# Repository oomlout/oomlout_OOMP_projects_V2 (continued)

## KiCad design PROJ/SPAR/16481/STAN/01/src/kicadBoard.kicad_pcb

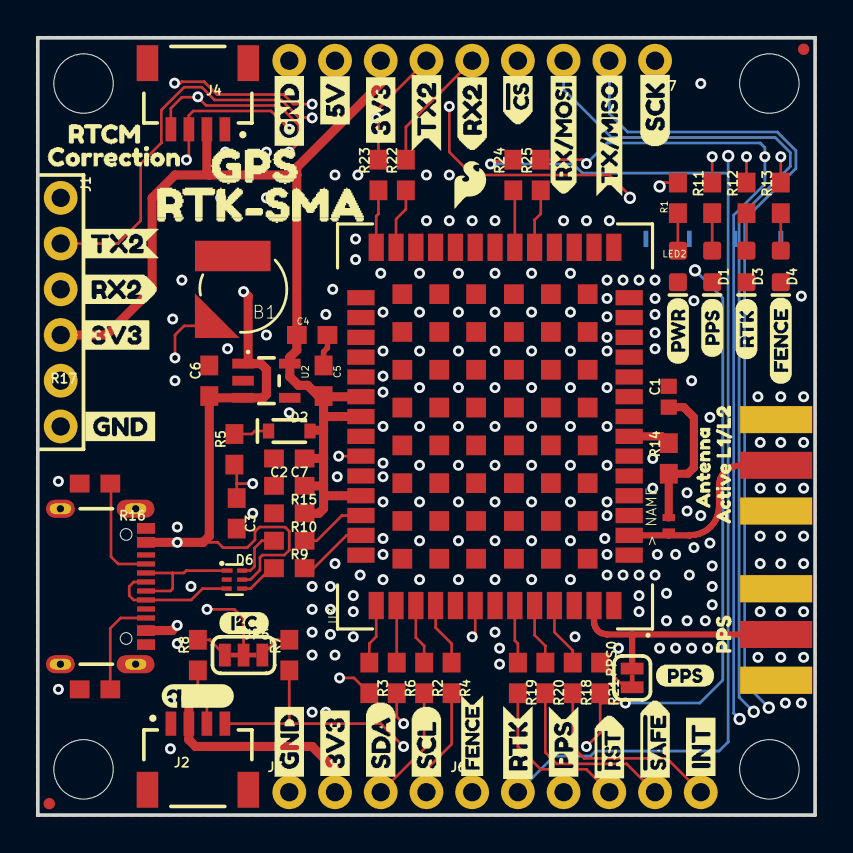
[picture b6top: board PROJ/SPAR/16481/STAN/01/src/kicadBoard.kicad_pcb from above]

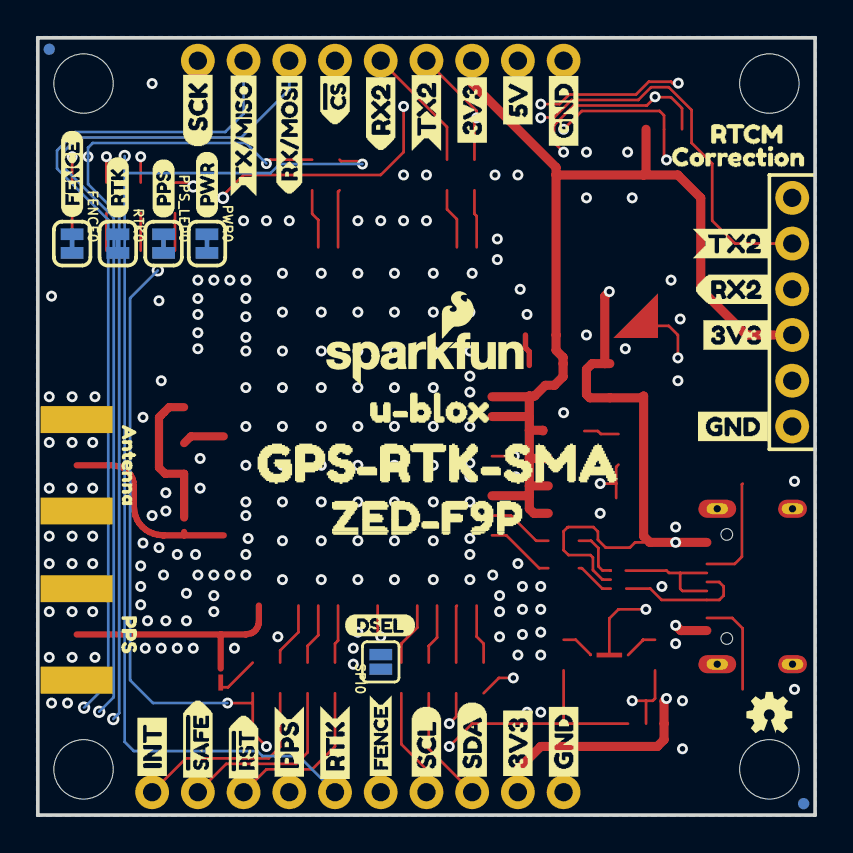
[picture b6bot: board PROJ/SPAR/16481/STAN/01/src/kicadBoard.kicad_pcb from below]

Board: 4 copper layers, 43.2 x 43.2 mm, 143 parts (44 on the bottom side), 52 nets.

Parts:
B1: 6.8MM_COIN_CELL; ML414H_IV01E
C1: 47pF; 0402
C2, C3, C4, C6: 1.0uF; 0603
C5, C7: 0.1uF; 0603
D1: Yellow; LED-0603
D2: 0.5A/40V/420mV; SOD-323
D3: GREEN; LED-0603
D4: BLUE; LED-0603
D6: PRTR5V0U2F; SOT886
E1, E2: SMA; SMA-EDGE
FB1: 120NH; 0402_MURATA
FENCE0: SMT-JUMPER_2_NC_TRACE_SILK
FRAME2: FRAME-LEDGER; CREATIVE_COMMONS
J1: Radio; 1X06_NO_SILK
J2, J4: Qwiic Right Angle; JST04_1MM_RA
J3: PTH; 1X04_NO_SILK
J5: USB-C-16P-2LAYER-PADS
J6: 1X06_NO_SILK
J7: 1X09_NO_SILK
JP5: SMT-JUMPER_3_2-NC_TRACE_SILK
JP21, JP61, JP71, JP81: FIDUCIALUFIDUCIAL; MICRO-FIDUCIAL
JP31, JP41, JP91, JP101: STAND-OFF
LED2: RED; LED-0603
LOGO1: OSHW-LOGOMINI; OSHW-LOGO-MINI
LOGO2: SFE_LOGO_NAME_FLAME.1_INCH; SFE_LOGO_NAME_FLAME_.1
PPS0: SMT-JUMPER_2_NC_TRACE_SILK
PPS_LED0: SMT-JUMPER_2_NC_TRACE_SILK
PWR0: SMT-JUMPER_2_NC_TRACE_SILK
R1, R5, R11, R12, R13: 1k; 0603
R2, R3, R4, R6, R14, R18, R19, R20, R21, R22, R23, R24, R25: 33; 0603
R7, R8: 2.2k; 0603
R9, R10: 27; 0603
R15: 100k; 0603
R16, R17: 5.1k; 0603
RTK0: SMT-JUMPER_2_NC_TRACE_SILK
SPI0: SMT-JUMPER_2_NO_SILK
U2: 3.3V; SOT23-5
U3: ZED-F9P
U$1, U$4: SDA-[)
U$2: SPECIAL_INSTRUCTIONS-ORDERING; ORDERING_INSTRUCTIONS
U$3, U$5: SCL-[)
U$6, U$7, U$60, U$61, U$66, U$67: 3V3-04
U$8, U$9, U$62, U$63: GND-04
U$10: I_SUPER2_C-()-03
U$11, U$54: FENCE2
U$12, U$18: PWR-()-03
U$13, U$28, U$29, U$32: RTK1
U$14, U$17: FENCE0
U$15, U$16: INT8
U$19, U$20: 5V
U$21, U$56, U$58: RX20
U$22: U#BLOX3
U$23, U$24: CS#-_]
U$25, U$52, U$72: PPS0
U$26, U$31: RX#MOSI3
U$27: DSEL0
U$30: QWIIC_4MM
U$33: SFE_LOGO_FLAME_.1
U$34, U$37: TX#MISO1
U$35, U$36: #RST3
U$38, U$41: SCK-(]-04
U$39, U$40: #SAFE1
U$42: RX22
U$43, U$44: PPS5
U$45, U$68: GND3
U$47, U$74: PPS1
U$48, U$70: RTCM5
U$49: ZED#F9P6
U$50, U$55, U$57: TX21
U$51: TX23
U$53, U$69: CORRECTION0
U$59: GPS0
U$65: ACTIVE_L1#L21
U$71, U$75: ANTENNA2
U$73: RTK#SMA4
U$76: GPS#RTK#SMA5

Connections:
3.3V: C2.1, C4.1, C5.2, C7.2, D2.A, J1.4, J2.2, J3.2, J4.2, J7.7, JP5.2, PWR0.2, R15.2, U2.5, U3.33, U3.34, U3.38
5V: C6.1, D6.5, J5.VBUS1, J5.VBUS2, J7.8, U2.1, U2.3
ANT_VCC: C1.1, FB1.P2, R14.1
BACKUP: B1.+, C3.1, R5.1, U3.36
CC1: J5.A5, R17.2
CC2: J5.B5, R16.2
D+: D6.4, R9.1
D-: D6.6, R10.1
D_SEL: SPI0.2, U3.47
FENCE_STAT: FENCE0.2, J6.1, R25.2
GND: B1.-, C1.2, C2.2, C3.2, C4.2, C5.1, C6.2, C7.1, D1.C, D3.C, D4.C, D6.2, E1.GND@0, E1.GND@1, E1.GND@2, E1.GND@3, E2.GND@0, E2.GND@1, E2.GND@2, E2.GND@3, J1.6, J2.1, J3.1, J4.1, J5.GND, J5.GND2, J5.SHLD1, J5.SHLD2, J5.SHLD3, J5.SHLD4, J7.9, LED2.C, R15.1, R16.1, R17.1, SPI0.1, U2.2, U3.1, U3.3, U3.12, U3.14, U3.32, U3.37, U3.41, U3.48, U3.55, U3.56, U3.57, U3.58, U3.59, U3.60, U3.61, U3.62, U3.63, U3.64, U3.65, U3.66, U3.67, U3.68, U3.69, U3.70, U3.71, U3.72, U3.73, U3.74, U3.75, U3.76, U3.77, U3.78, U3.79, U3.80, U3.81, U3.82, U3.83, U3.84, U3.85, U3.86, U3.87, U3.88, U3.89, U3.90, U3.91, U3.92, U3.93, U3.94, U3.95, U3.96, U3.97, U3.98, U3.99, U3.100, U3.101, U3.102
GPS_ANT1: E1.SIG, FB1.P1, U3.2
INT: J6.6, R18.2
unnamed: D3.A, R12.1
unnamed: D1.A, R11.1
unnamed: R12.2, RTK0.1
unnamed: PPS_LED0.1, R11.2
unnamed: JP5.1, R8.2
unnamed: D2.C, R5.2
unnamed: D4.A, R13.1
unnamed: JP5.3, R7.2
unnamed: FENCE0.1, R13.2
unnamed: LED2.A, R1.1
unnamed: R9.2, U3.40
unnamed: R10.2, U3.39
unnamed: R14.2, U3.7
unnamed: R22.1, U3.26
unnamed: R18.1, U3.51
unnamed: R19.1, U3.49
unnamed: PWR0.1, R1.2
unnamed: R20.1, U3.50
unnamed: R24.1, U3.20
unnamed: R25.1, U3.19
unnamed: PPS0.1, R21.1
PPS: E2.SIG, PPS0.2, U3.53
PPS_STAT: J6.3, PPS_LED0.2, R21.2
RTK_STAT: J6.2, R24.2, RTK0.2
RX2: J1.3, J7.5, R22.2
RXI/MOSI: J7.3, R6.2
RXLV: R6.1, U3.43
SCL/SCK: J2.4, J3.4, J4.4, J7.1, R4.2, R7.1
SCL_LV: R4.1, U3.45
SDA/~CS: J2.3, J3.3, J4.3, J7.4, R2.2, R8.1
SDA_LV: R2.1, U3.44
TX2: J1.2, J7.6, R23.2
TX2_P: R23.1, U3.27
TXLV: R3.1, U3.42
TXO/MISO: J7.2, R3.2
UNP_D+: D6.3, J5.A6, J5.B6
UNP_D-: D6.1, J5.A7, J5.B7
~RESET: J6.4, R19.2
~SAFE: J6.5, R20.2

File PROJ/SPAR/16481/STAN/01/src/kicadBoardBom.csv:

"Id";"Designator";"Package";"Quantity";"Designation";"Supplier and ref";
1;"R25,R23,R6,R19,R18,R2,R20,R3,R22,R14,R24,R4,R21";"0603";13;"33";;;
2;"U$63,U$8,U$9,U$62";"GND-04";4;"";;;
3;"JP101,JP41,JP91,JP31";"STAND-OFF";4;"STAND-OFF";;;
4;"U$50,U$55,U$57";"TX21";3;"";;;
5;"U$59";"GPS0";1;"";;;
6;"U2";"SOT23-5";1;"3.3V";;;
7;"R12,R11,R13,R5,R1";"0603";5;"1k";;;
8;"U$61,U$66,U$6,U$60,U$67,U$7";"3V3-04";6;"";;;
9;"U$42";"RX22";1;"";;;
10;"U$2";"ORDERING_INSTRUCTIONS";1;"SPECIAL_INSTRUCTIONS-ORDERING";;;
11;"R15";"0603";1;"100k";;;
12;"U$70,U$48";"RTCM5";2;"";;;
13;"FRAME2";"CREATIVE_COMMONS";1;"FRAME-LEDGER";;;
14;"U$47,U$74";"PPS1";2;"";;;
15;"B1";"ML414H_IV01E";1;"6.8MM_COIN_CELL";;;
16;"J4,J2";"JST04_1MM_RA";2;"Qwiic Right Angle";;;
17;"LED2";"LED-0603";1;"RED";;;
18;"U$11,U$54";"FENCE2";2;"";;;
19;"U$69,U$53";"CORRECTION0";2;"";;;
20;"U$26,U$31";"RX#MOSI3";2;"";;;
21;"C3,C4,C2,C6";"0603";4;"1.0uF";;;
22;"U$52,U$72,U$25";"PPS0";3;"";;;
23;"U$45,U$68";"GND3";2;"";;;
24;"C5,C7";"0603";2;"0.1uF";;;
25;"U$39,U$40";"#SAFE1";2;"";;;
26;"R17,R16";"0603";2;"5.1k";;;
27;"U$21,U$56,U$58";"RX20";3;"";;;
28;"U$19,U$20";"5V";2;"";;;
29;"J3";"1X04_NO_SILK";1;"PTH";;;
30;"U$1,U$4";"SDA-[)";2;"";;;
31;"U3";"ZED-F9P";1;"ZED-F9P";;;
32;"D2";"SOD-323";1;"0.5A/40V/420mV";;;
33;"U$15,U$16";"INT8";2;"";;;
34;"U$51";"TX23";1;"";;;
35;"E2,E1";"SMA-EDGE";2;"SMA";;;
36;"C1";"0402";1;"47pF";;;
37;"U$3,U$5";"SCL-[)";2;"";;;
38;"U$18,U$12";"PWR-()-03";2;"";;;
39;"U$13,U$29,U$28,U$32";"RTK1";4;"";;;
40;"J1";"1X06_NO_SILK";1;"Radio";;;
41;"U$23,U$24";"CS#-_]";2;"";;;
42;"PPS0,PPS_LED0,RTK0,FENCE0,PWR0";"SMT-JUMPER_2_NC_TRACE_SILK";5;"";;;
43;"U$10";"I_SUPER2_C-()-03";1;"";;;
44;"D3";"LED-0603";1;"GREEN";;;
45;"R10,R9";"0603";2;"27";;;
46;"U$14,U$17";"FENCE0";2;"";;;
47;"JP21,JP61,JP71,JP81";"MICRO-FIDUCIAL";4;"FIDUCIALUFIDUCIAL";;;
48;"U$38,U$41";"SCK-(]-04";2;"";;;
49;"FB1";"0402_MURATA";1;"120NH";;;
50;"R8,R7";"0603";2;"2.2k";;;
51;"U$30";"QWIIC_4MM";1;"";;;
52;"D6";"SOT886";1;"PRTR5V0U2F";;;
53;"J5";"USB-C-16P-2LAYER-PADS";1;"";;;
54;"U$33";"SFE_LOGO_FLAME_.1";1;"";;;
55;"U$43,U$44";"PPS5";2;"";;;
56;"D4";"LED-0603";1;"BLUE";;;
57;"U$73";"RTK#SMA4";1;"";;;
58;"J7";"1X09_NO_SILK";1;"";;;
59;"JP5";"SMT-JUMPER_3_2-NC_TRACE_SILK";1;"";;;
60;"U$34,U$37";"TX#MISO1";2;"";;;
61;"U$65";"ACTIVE_L1#L21";1;"";;;
62;"J6";"1X06_NO_SILK";1;"";;;
63;"U$71,U$75";"ANTENNA2";2;"";;;
64;"D1";"LED-0603";1;"Yellow";;;
65;"U$35,U$36";"#RST3";2;"";;;
66;"SPI0";"SMT-JUMPER_2_NO_SILK";1;"";;;
67;"LOGO1";"OSHW-LOGO-MINI";1;"OSHW-LOGOMINI";;;
68;"U$27";"DSEL0";1;"";;;
69;"U$49";"ZED#F9P6";1;"";;;
70;"U$76";"GPS#RTK#SMA5";1;"";;;
71;"LOGO2";"SFE_LOGO_NAME_FLAME_.1";1;"SFE_LOGO_NAME_FLAME.1_INCH";;;
72;"U$22";"U#BLOX3";1;"";;;

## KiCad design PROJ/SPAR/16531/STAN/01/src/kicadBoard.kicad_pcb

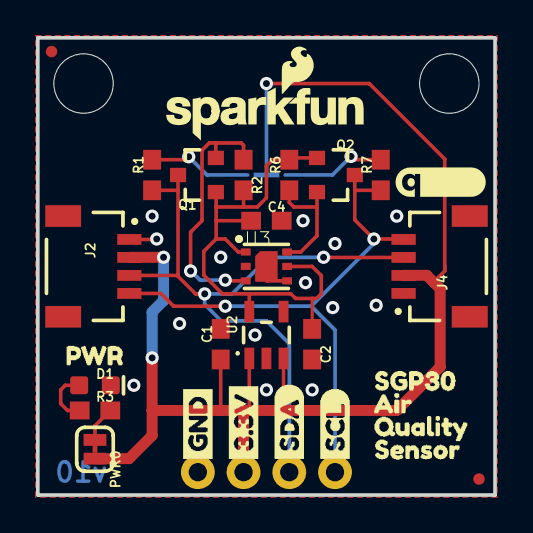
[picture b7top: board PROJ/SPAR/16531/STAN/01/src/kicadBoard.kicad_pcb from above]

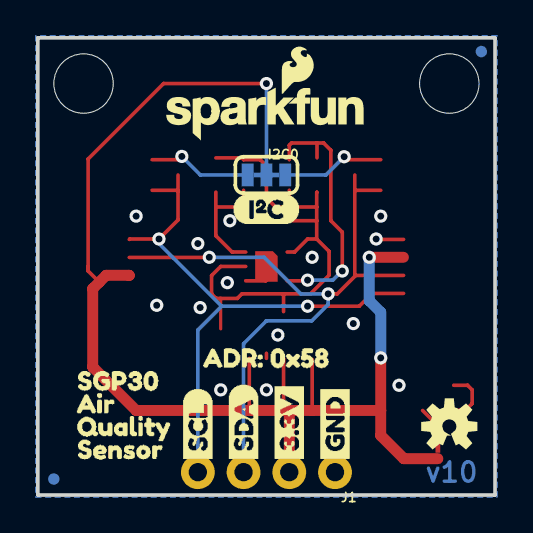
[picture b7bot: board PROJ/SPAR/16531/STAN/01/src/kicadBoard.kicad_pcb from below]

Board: 2 copper layers, 25.4 x 25.4 mm, 49 parts (16 on the bottom side), 11 nets.

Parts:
C1, C2: 1.0uF; 0603
C4: 0.1uF; 0603
D1: RED; LED-0603
FRAME1: FRAME-LETTER; CREATIVE_COMMONS
I2C0: JUMPER-SMT_3_2-NC_TRACE_SILK; SMT-JUMPER_3_2-NC_TRACE_SILK
J1: 1X04_NO_SILK
J2, J4: QWIIC_RIGHT_ANGLE; JST04_1MM_RA
JP1, JP2, JP5, JP6: FIDUCIALUFIDUCIAL; MICRO-FIDUCIAL
JP3, JP4: STAND-OFF
LOGO2: REVISION
LOGO3, LOGO4: SFE_LOGO_NAME_FLAME.1_INCH; SFE_LOGO_NAME_FLAME_.1
LOGO5: OSHW-LOGOS; OSHW-LOGO-S
PWR0: JUMPER-SMT_2_NC_TRACE_SILK; SMT-JUMPER_2_NC_TRACE_SILK
Q1, Q2: 220mA/50V/3.5Ω; SOT23-3
R1, R2, R6, R7: 10k; 0603
R3: 1k; 0603
U2: AP2127K-1.8V; SOT23-5
U3: SGP30
U$1, U$11: _AIR1
U$2, U$12: QUALITY2
U$3, U$22: GND1
U$4, U$21: 3#3V2
U$5, U$27: SDA8
U$6, U$26: SCL9
U$7, U$13: SENSOR3
U$8, U$9: SGP300
U$14: ADR#_0X580
U$15: I2C
U$16: QWIIC_5MM
U$17: PWR_TO

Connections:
1.8V: C2.1, C4.1, Q1.1, Q2.1, R2.2, R6.2, U2.5, U3.1, U3.5
3.3V: C1.1, I2C0.2, J1.2, J2.2, J4.2, PWR0.2, U2.1, U2.3
GND: C1.2, C2.2, C4.2, D1.C, J1.1, J2.1, J4.1, U2.2, U3.2, U3.4, U3.DIEPAD
LSCL: Q2.2, R6.1, U3.6
LSDA: Q1.2, R2.1, U3.3
unnamed: PWR0.1, R3.2
unnamed: I2C0.3, R1.2
unnamed: D1.A, R3.1
unnamed: I2C0.1, R7.2
SCL: J1.4, J2.4, J4.4, Q2.3, R7.1
SDA: J1.3, J2.3, J4.3, Q1.3, R1.1

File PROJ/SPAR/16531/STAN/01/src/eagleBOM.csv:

"Part";"Value";"Device";"Package";"Description";"DESIGNER";"PROD_ID";"REV";"VALUE";
"C1";"1.0uF";"1.0UF-0603-16V-10%";"0603";"1µF ceramic capacitors";"";"CAP-00868";"";"1.0uF";
"C2";"1.0uF";"1.0UF-0603-16V-10%";"0603";"1µF ceramic capacitors";"";"CAP-00868";"";"1.0uF";
"C4";"0.1uF";"0.1UF-0603-25V-(+80/-20%)";"0603";"0.1µF ceramic capacitors";"";"CAP-00810";"";"0.1uF";
"D1";"RED";"LED-RED0603";"LED-0603";"Red SMD LED";"";"DIO-00819";"";"RED";
"FRAME1";"FRAME-LETTER";"FRAME-LETTER";"CREATIVE_COMMONS";"Schematic Frame - Letter";"";"";"";"";
"I2C";"JUMPER-SMT_3_2-NC_TRACE_SILK";"JUMPER-SMT_3_2-NC_TRACE_SILK";"SMT-JUMPER_3_2-NC_TRACE_SILK";"Normally closed trace jumper (2 of 2 connections)";"";"";"";"";
"J1";"";"CONN_041X04_NO_SILK";"1X04_NO_SILK";"Multi connection point. Often used as Generic Header-pin footprint for 0.1 inch spaced/style header connections";"";"CONN-09696";"";"";
"J2";"QWIIC_RIGHT_ANGLE";"QWIIC_CONNECTORJS-1MM";"JST04_1MM_RA";"SparkFun I2C Standard Qwiic Connector";"";"CONN-13694";"";"QWIIC_RIGHT_ANGLE";
"J4";"QWIIC_RIGHT_ANGLE";"QWIIC_CONNECTORJS-1MM";"JST04_1MM_RA";"SparkFun I2C Standard Qwiic Connector";"";"CONN-13694";"";"QWIIC_RIGHT_ANGLE";
"JP1";"FIDUCIALUFIDUCIAL";"FIDUCIALUFIDUCIAL";"MICRO-FIDUCIAL";"Fiducial Alignment Points";"";"";"";"";
"JP2";"FIDUCIALUFIDUCIAL";"FIDUCIALUFIDUCIAL";"MICRO-FIDUCIAL";"Fiducial Alignment Points";"";"";"";"";
"JP3";"STAND-OFF";"STAND-OFF";"STAND-OFF";"Stand Off";"";"";"";"";
"JP4";"STAND-OFF";"STAND-OFF";"STAND-OFF";"Stand Off";"";"";"";"";
"JP5";"FIDUCIALUFIDUCIAL";"FIDUCIALUFIDUCIAL";"MICRO-FIDUCIAL";"Fiducial Alignment Points";"";"";"";"";
"JP6";"FIDUCIALUFIDUCIAL";"FIDUCIALUFIDUCIAL";"MICRO-FIDUCIAL";"Fiducial Alignment Points";"";"";"";"";
"LOGO2";"REVISION";"REVISION";"REVISION";""Revision By" Text";"";"";"";"";
"LOGO3";"SFE_LOGO_NAME_FLAME.1_INCH";"SFE_LOGO_NAME_FLAME.1_INCH";"SFE_LOGO_NAME_FLAME_.1";"SparkFun Font Logo w/ Flame";"";"";"";"";
"LOGO4";"SFE_LOGO_NAME_FLAME.1_INCH";"SFE_LOGO_NAME_FLAME.1_INCH";"SFE_LOGO_NAME_FLAME_.1";"SparkFun Font Logo w/ Flame";"";"";"";"";
"LOGO5";"OSHW-LOGOS";"OSHW-LOGOS";"OSHW-LOGO-S";"Open-Source Hardware (OSHW) Logo";"";"";"";"";
"PWR";"JUMPER-SMT_2_NC_TRACE_SILK";"JUMPER-SMT_2_NC_TRACE_SILK";"SMT-JUMPER_2_NC_TRACE_SILK";"Normally closed trace jumper";"";"";"";"";
"Q1";"220mA/50V/3.5Ω";"MOSFET-NCH-BSS138";"SOT23-3";"N-channel MOSFETs";"";"TRANS-00830";"";"220mA/50V/3.5Ω";
"Q2";"220mA/50V/3.5Ω";"MOSFET-NCH-BSS138";"SOT23-3";"N-channel MOSFETs";"";"TRANS-00830";"";"220mA/50V/3.5Ω";
"R1";"10k";"10KOHM-0603-1/10W-1%";"0603";"10kΩ resistor";"";"RES-00824";"";"10k";
"R2";"10k";"10KOHM-0603-1/10W-1%";"0603";"10kΩ resistor";"";"RES-00824";"";"10k";
"R3";"1k";"1KOHM-0603-1/10W-1%";"0603";"1kΩ resistor";"";"RES-07856";"";"1k";
"R6";"10k";"10KOHM-0603-1/10W-1%";"0603";"10kΩ resistor";"";"RES-00824";"";"10k";
"R7";"10k";"10KOHM-0603-1/10W-1%";"0603";"10kΩ resistor";"";"RES-00824";"";"10k";
"U2";"AP2127K-1.8V";"V_REG_AP2127K-1.8V";"SOT23-5";"AP2127 - 300mA CMOS LDO Regulator w/ Enable";"";"VREG-14239";"";"AP2127K-1.8V";
"U3";"SGP30";"SGP30";"SGP30";"The SGP30 is a digital multi-pixel gas sensor designed for";"";"IC-14776";"";"SGP30";

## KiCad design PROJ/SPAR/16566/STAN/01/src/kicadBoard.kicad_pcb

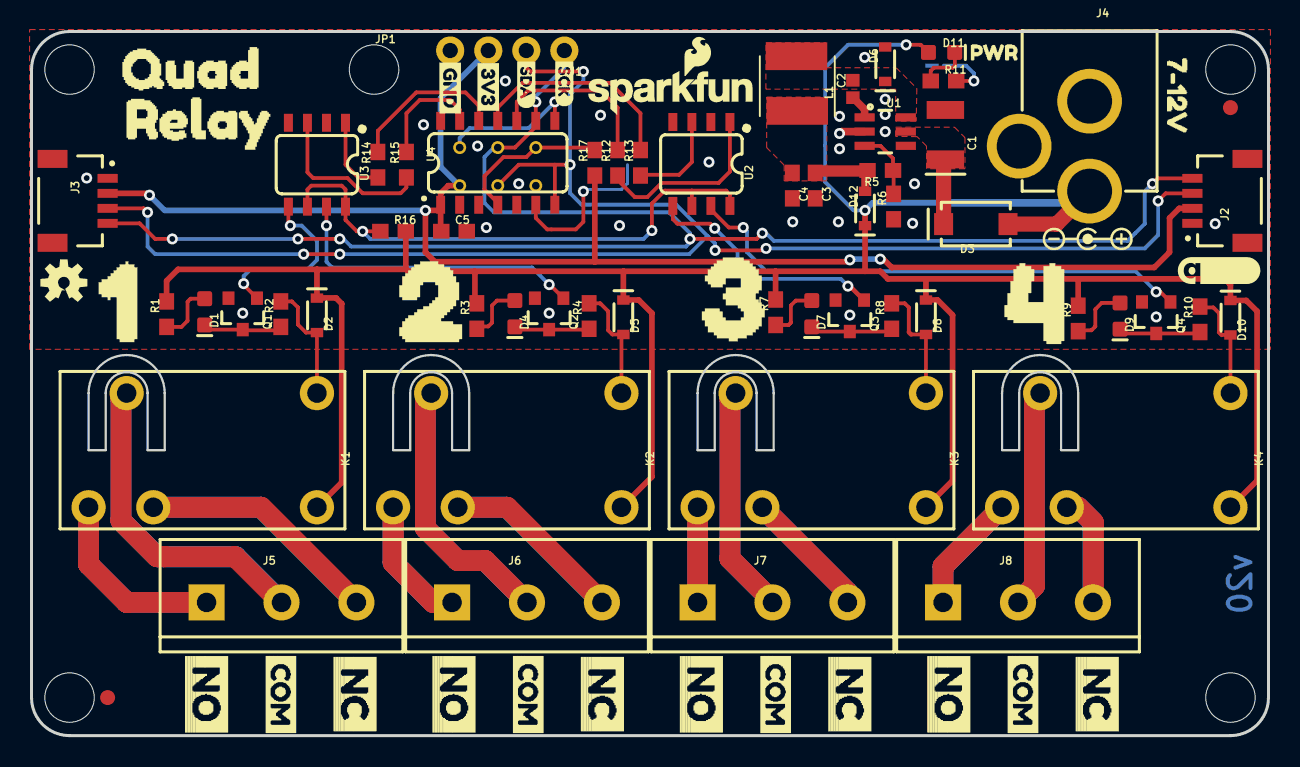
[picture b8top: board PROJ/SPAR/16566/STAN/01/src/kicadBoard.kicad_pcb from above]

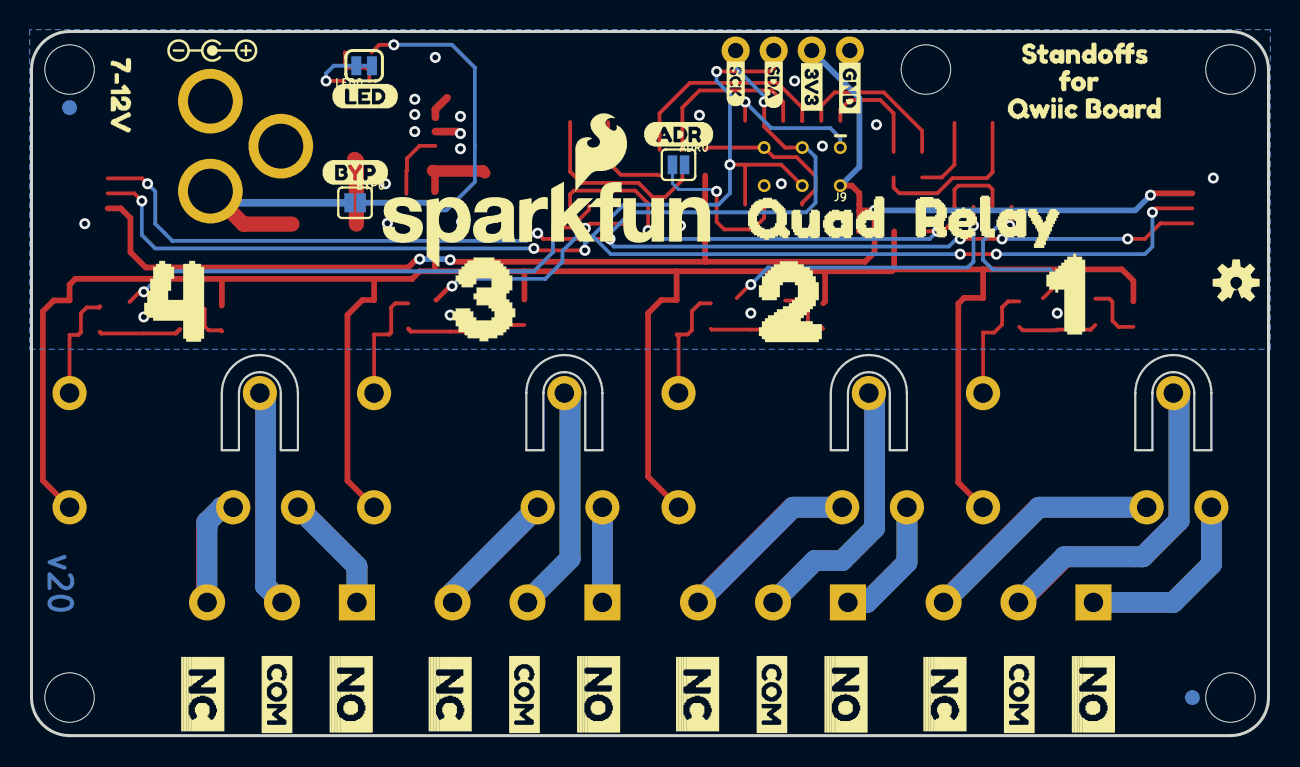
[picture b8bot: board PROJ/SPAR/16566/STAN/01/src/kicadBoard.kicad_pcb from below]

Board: 2 copper layers, 82.6 x 47.0 mm, 129 parts (38 on the bottom side), 53 nets.

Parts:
ADR0: JUMPER-SMT_2_NO_SILK; SMT-JUMPER_2_NO_SILK
BYP0: JUMPER-SMT_2_NO_SILK; SMT-JUMPER_2_NO_SILK
C1: 10uF; EIA3528
C2: 0.1uF; 0402
C3, C4: 10uF; 0603
C5: 0.1uF; 0603
D1, D4, D7, D9: BLUE; LED-0603
D2, D5, D8, D10: 1A/23V/620mV; SOD-323
D3: 1A/40V/500mV; SMA-DIODE
D6, D12: 3A/10V/280mV; SOD-323
D11: RED; LED-0603
FD1, FD2, FD3, FD4: FIDUCIAL1X2; FIDUCIAL-1X2
FRAME1: FRAME-LEDGER; CREATIVE_COMMONS
J1: 1X04_NO_SILK
J2, J3: Qwiic Right Angle; JST04_1MM_RA
J4: POWER_JACK; POWER_JACK_PTH
J5, J6, J7, J8: SCREWTERMINAL-5MM-3
J9: AVR_SPI_PROG_3X2TESTPOINTS; 2X3_TEST_POINTS
JP1, JP4, JP5, JP6, JP7: STAND-OFF
K1, K2, K3, K4: RELAY-SPDT-JZC-11F; RELAY-JZC
L1: 15uH; INDUCTOR_15UH
LED0: JUMPER-SMT_2_NC_TRACE_SILK; SMT-JUMPER_2_NC_TRACE_SILK
LOGO1: SFE_LOGO_NAME_FLAME.1_INCH; SFE_LOGO_NAME_FLAME_.1
LOGO2: OSHW-LOGOS; OSHW-LOGO-S
Q1, Q2, Q3, Q4: 600mA/40V; SOT23-3
R1, R3, R7, R9, R11: 1k; 0603
R2, R4, R8, R10: 0; 0603
R5: 12k; 0603
R6: 2.0k; 0603
R12, R13, R14, R15: 100; 0603
R16: 330; 0603
R17: 10k; 0603
U1: LMR14010A; SOT23-6
U2, U3: DUAL-OPTOISOLATOR_SOIC8; SO08
U4: ATTINY84-ARDUINO; SO14
U$1, U$49: 7#12V0
U$2, U$40: 20
U$3, U$39: 10
U$4, U$41: 30
U$5, U$42: 40
U$6, U$43: QUAD0
U$7, U$44: RELAY0
U$8, U$48: SCK-[)-03
U$9, U$45: GND-03
U$10, U$12: 3V3-03
U$11, U$47: SDA0
U$13: OSHW-LOGO-S
U$14: BYP
U$15, U$18, U$21, U$24, U$27, U$30, U$33, U$36: NO0
U$16, U$19, U$22, U$25, U$28, U$31, U$34, U$37: COM0
U$17, U$20, U$23, U$26, U$29, U$32, U$35, U$38: NC0
U$46: PWR_TO
U$50: STANDOFFS0
U$51, U$54: POLARITY_MARKING_CENTER_POSITIVE#JPG
U$52: FOR1
U$53: LED
U$55: QWIIC_5.5MM
U$56: ADR-()-04
U$57: SFE_LOGO_NAME_FLAME_.2
U$58: QWIIC_BOARD2

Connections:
3.3V: C5.1, J1.3, J2.2, J3.2, J9.2, R17.1, U4.1
5V: BYP0.2, D2.C, D5.C, D8.C, D10.C, D11.A, D12.C, K1.5, K2.5, K3.5, K4.5, R1.2, R3.2, R7.2, R9.2, R16.2
5V_OUT: C3.1, C4.1, D12.A, L1.P2, R5.2
ADDR_JUMP: ADR0.1, U4.6
CB: C2.1, U1.1
COM1: J5.2, K1.4
COM2: J6.2, K2.4
COM3: J7.2, K3.4
COM4: J8.2, K4.4
FB: R5.1, R6.2, U1.3
GND: ADR0.2, C1.C, C3.2, C4.2, C5.2, D6.A, J1.4, J2.1, J3.1, J4.GND, J4.GNDBREAK, J9.6, LED0.1, Q1.2, Q2.2, Q3.2, Q4.2, R6.1, U1.2, U2.2, U2.4, U3.2, U3.4, U4.14
MISO: J9.1, U4.8
unnamed: D1.A, R1.1
unnamed: D1.C, Q1.3, R2.1
unnamed: R15.1, U3.3
unnamed: D4.A, R3.1
unnamed: R14.1, U3.1
unnamed: R16.1, U2.6, U2.8, U3.6, U3.8
unnamed: D7.A, R7.1
unnamed: D9.A, R9.1
unnamed: R12.1, U2.1
unnamed: D2.A, K1.1, R2.2
unnamed: R13.1, U2.3
unnamed: D4.C, Q2.3, R4.1
unnamed: D11.C, R11.1
unnamed: LED0.2, R11.2
unnamed: D7.C, Q3.3, R8.1
unnamed: D9.C, Q4.3, R10.1
unnamed: D5.A, K2.1, R4.2
unnamed: D8.A, K3.1, R8.2
unnamed: D10.A, K4.1, R10.2
NC1: J5.3, K1.2
NC2: J6.3, K2.2
NC3: J7.3, K3.2
NC4: J8.3, K4.2
NO1: J5.1, K1.3
NO2: J6.1, K2.3
NO3: J7.1, K3.3
NO4: J8.1, K4.3
OPTO_1: Q1.1, U3.5
OPTO_2: Q2.1, U3.7
OPTO_3: Q3.1, U2.5
OPTO_4: Q4.1, U2.7
RELAY_CTRL1: R12.2, U4.10
RELAY_CTRL2: R13.2, U4.11
RELAY_CTRL3: R14.2, U4.12
RELAY_CTRL4: R15.2, U4.13
SCL/SCK: J1.1, J2.4, J3.4, J9.3, U4.9
SDA/MOSI: J1.2, J2.3, J3.3, J9.4, U4.7
SW: C2.2, D6.C, L1.P1, U1.6
VIN: BYP0.1, D3.A, J4.PWR
VIN_DC_DC: C1.A, D3.C, U1.5
~RESET: J9.5, R17.2, U4.4
